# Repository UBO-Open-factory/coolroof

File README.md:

# coolroof
Développement des capteurs TOCIO pour CoolRoof

Insérer le schéma de l'architecture du projet

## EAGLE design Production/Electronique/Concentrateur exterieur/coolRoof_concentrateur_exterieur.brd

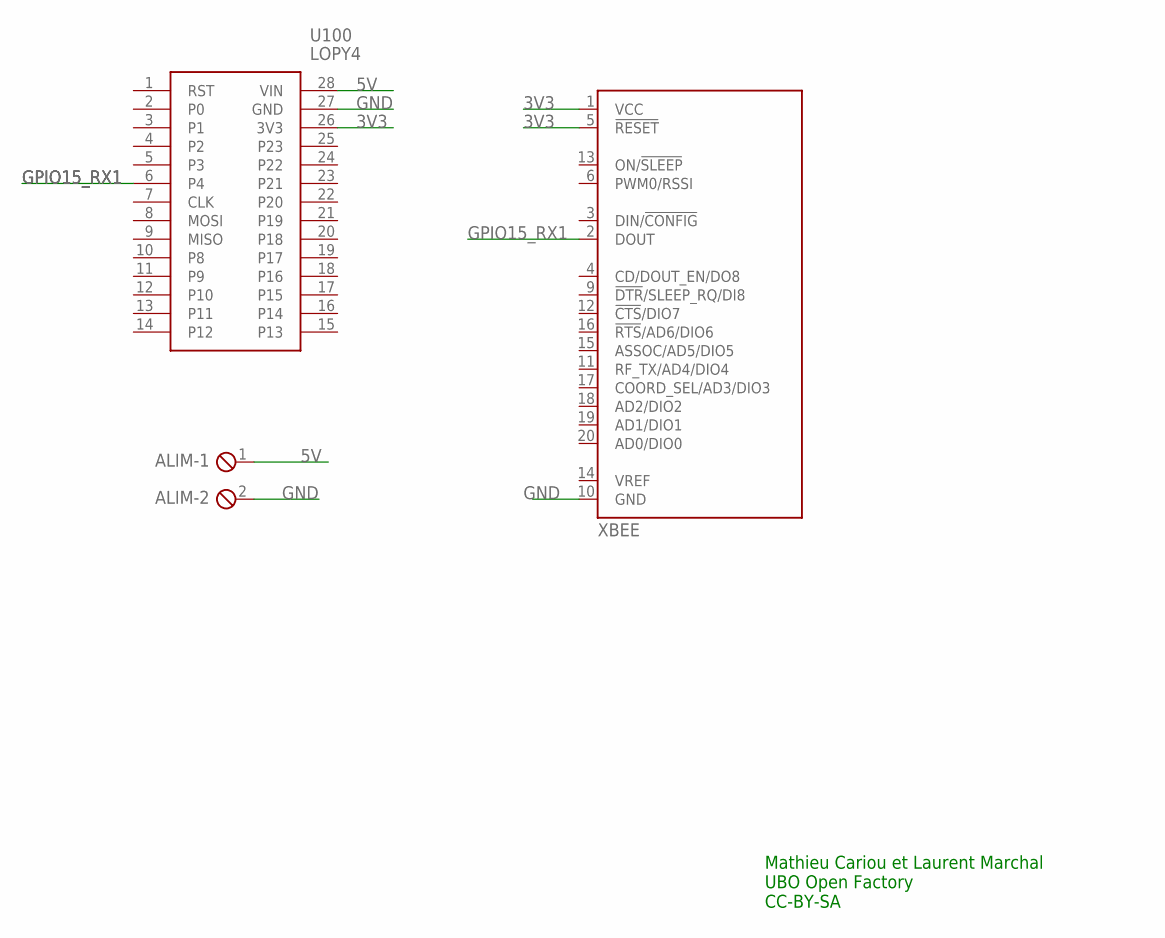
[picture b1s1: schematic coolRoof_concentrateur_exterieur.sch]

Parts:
ALIM: MPT2; 2POL254
U100: LOPY4
U101: XBEE

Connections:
3V3: U100.26 (3V3), U101.1 (VCC), U101.5 (!RESET)
5V: ALIM.1, U100.28 (VIN)
GND: ALIM.2, U100.27 (GND), U101.10 (GND)
GPIO15_RX1: U100.6 (P4), U101.2 (DOUT)

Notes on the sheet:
Mathieu Cariou et Laurent Marchal UBO Open Factory CC-BY-SA

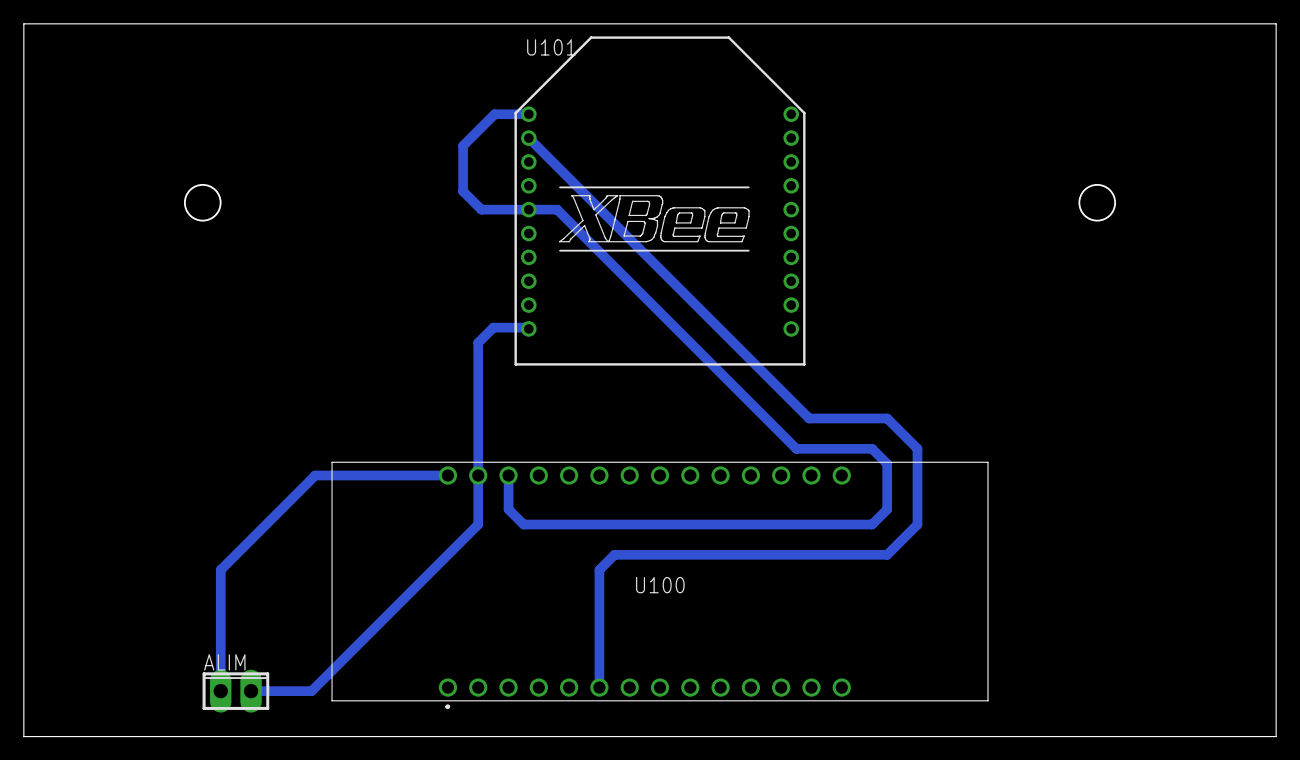
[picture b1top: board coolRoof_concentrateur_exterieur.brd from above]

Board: 2 copper layers, 105.0 x 59.8 mm, 3 parts (0 on the bottom side), 4 nets.

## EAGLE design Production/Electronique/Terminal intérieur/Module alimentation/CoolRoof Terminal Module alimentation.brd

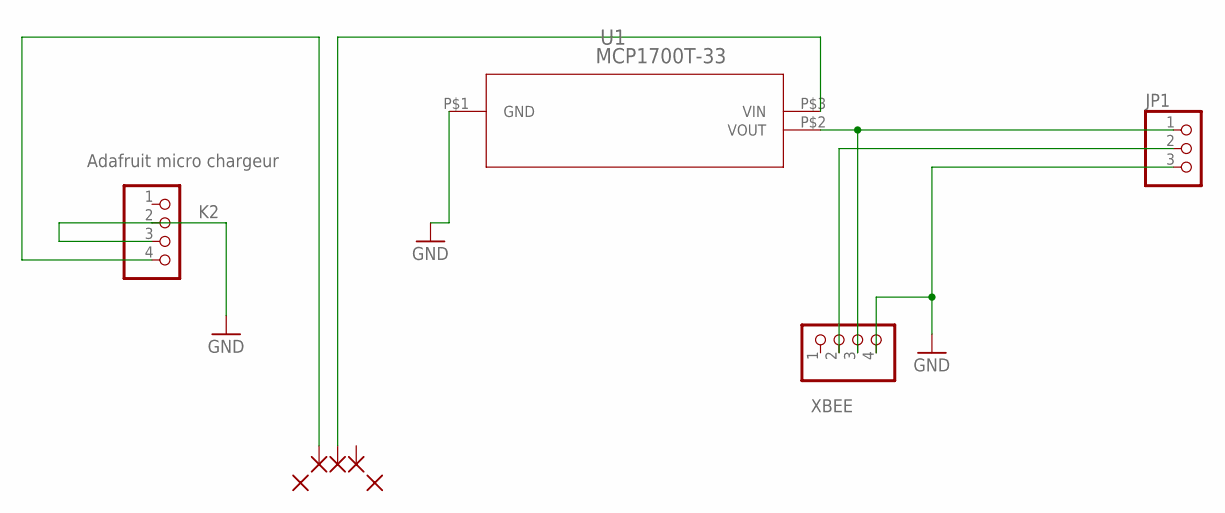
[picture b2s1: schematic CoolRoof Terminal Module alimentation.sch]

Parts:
JP1: PINHD-1X3; 1X03
K2: Adafruit micro chargeur; 1X04
PAD1, PAD2, PAD3: 1,6/0,8
PAD4, PAD5: N_2,0/1,5; 2,0/1,5
U1: MCP1700T-33; SOT-23
XBEE: PINHD-1X4; 1X04

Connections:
GND: JP1.3, K2.2, K2.3, U1.P$1 (GND), XBEE.4
unnamed: JP1.1, U1.P$2 (VOUT), XBEE.3
unnamed: JP1.2, XBEE.2
unnamed: K2.4, PAD1.1
unnamed: PAD2.1, U1.P$3 (VIN)

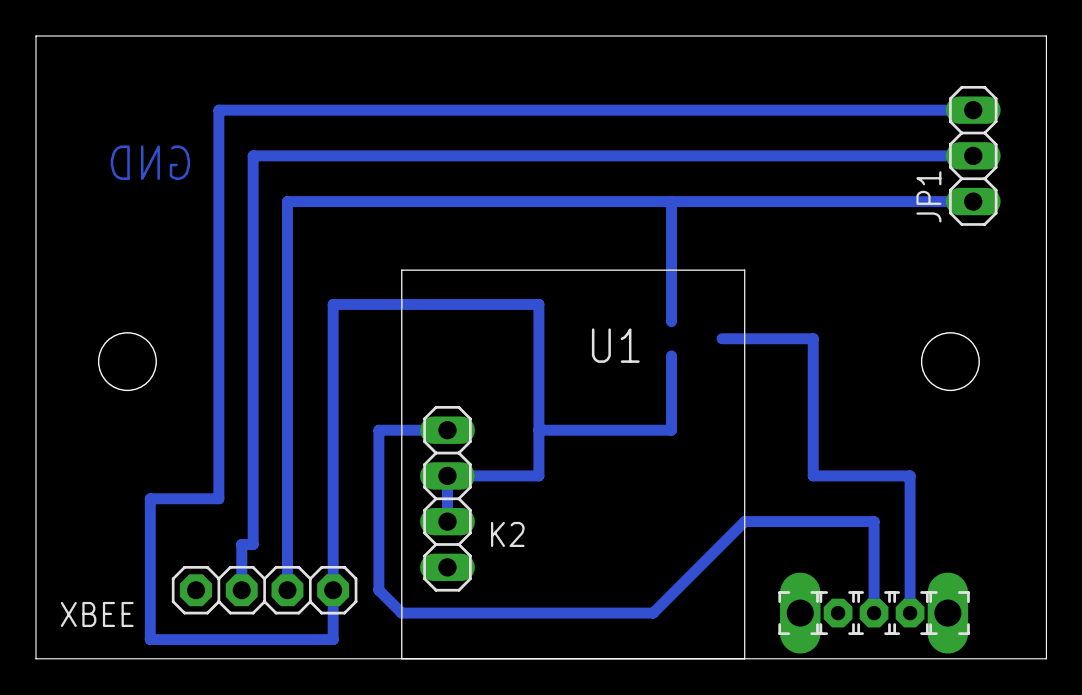
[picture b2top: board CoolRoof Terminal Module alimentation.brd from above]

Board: 2 copper layers, 56.1 x 34.6 mm, 9 parts (1 on the bottom side), 5 nets.

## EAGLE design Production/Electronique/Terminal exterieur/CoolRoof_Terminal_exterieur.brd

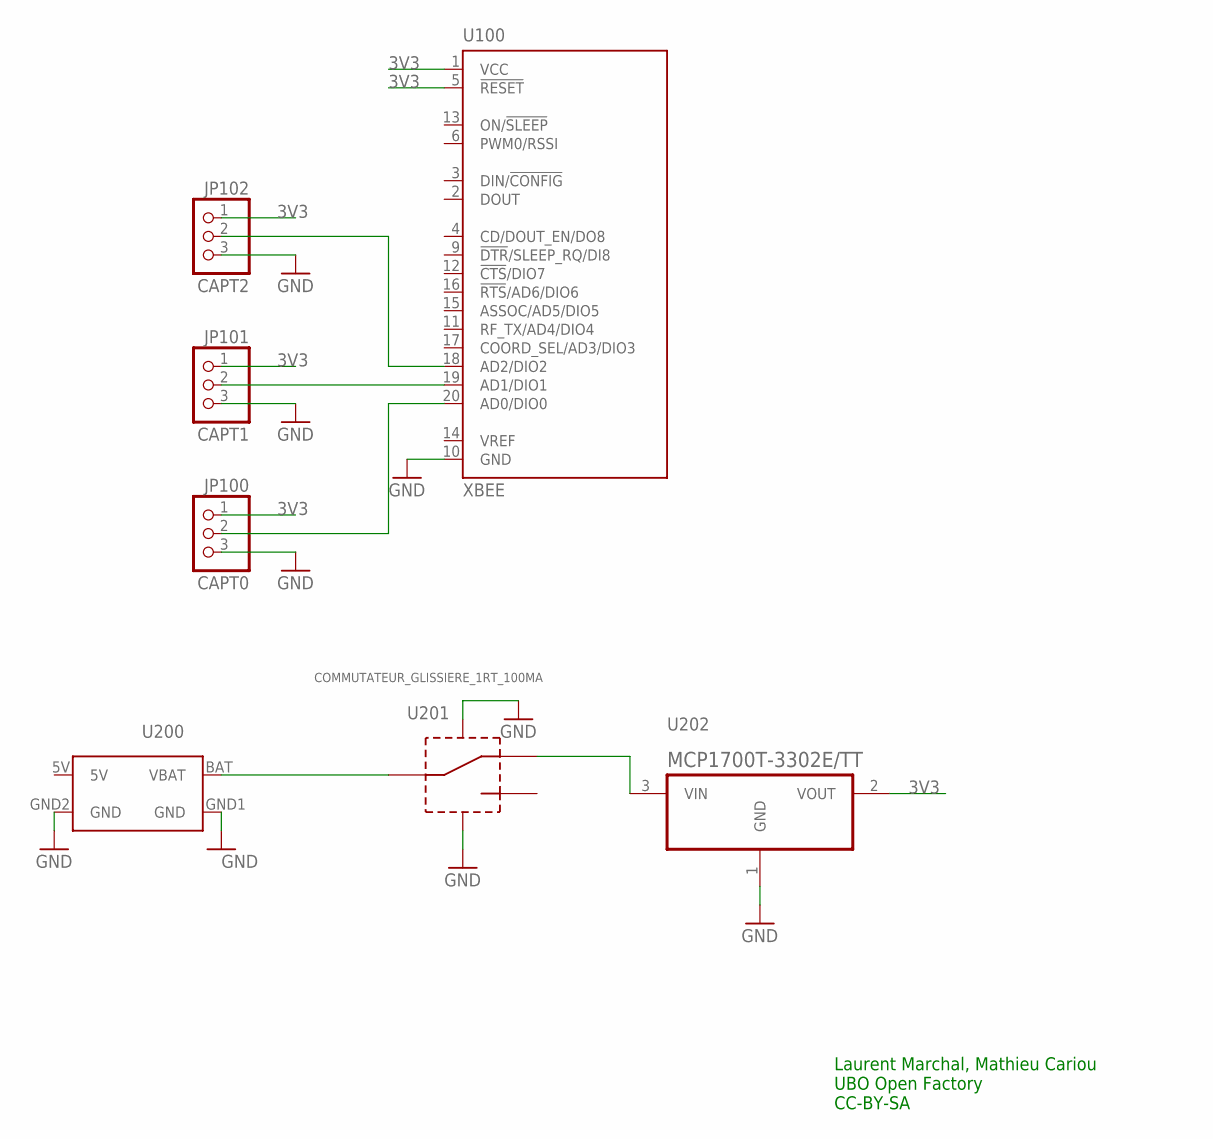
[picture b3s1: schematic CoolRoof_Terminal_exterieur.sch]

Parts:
JP100: CAPT0; 1X03
JP101: CAPT1; 1X03
JP102: CAPT2; 1X03
U100: XBEE
U200: MICROUSB-LIPO-CHARGEUR-ADAFRUITMICRO-USB-CHARGEUR; MICROUSB-LIPO-CHARGEUR-ADAFRUIT
U201: COMMUTATEUR_GLISSIERE_1RT_100MA
U202: MCP1700T-3302E/TT; SOT95P237X112-3N

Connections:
3V3: JP100.1, JP101.1, JP102.1, U100.1 (VCC), U100.5 (!RESET), U202.2 (VOUT)
GND: JP100.3, JP101.3, JP102.3, U100.10 (GND), U200.GND1 (GND), U200.GND2 (GND), U201.GNDA, U201.GNDB, U202.1 (GND)
unnamed: JP100.2, U100.20 (AD0/DIO0)
unnamed: U200.BAT (VBAT), U201.COM
unnamed: U201.OUTB (OUT2), U202.3 (VIN)
unnamed: JP101.2, U100.19 (AD1/DIO1)
unnamed: JP102.2, U100.18 (AD2/DIO2)

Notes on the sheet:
Laurent Marchal, Mathieu Cariou UBO Open Factory CC-BY-SA

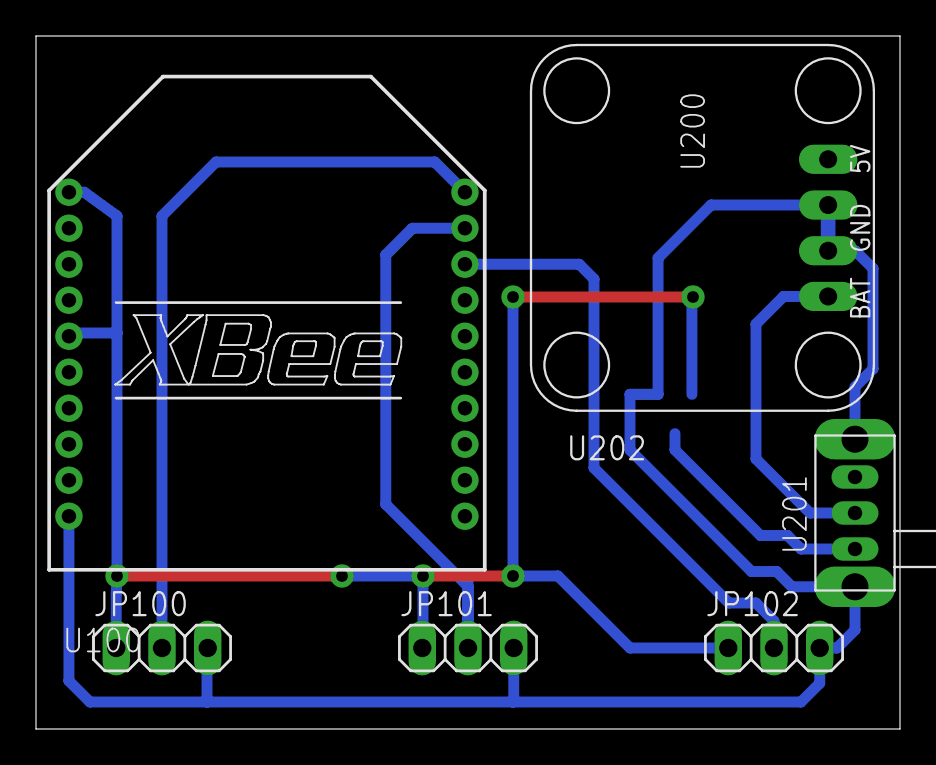
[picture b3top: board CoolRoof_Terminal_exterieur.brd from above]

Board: 2 copper layers, 48.0 x 38.5 mm, 7 parts (1 on the bottom side), 7 nets.

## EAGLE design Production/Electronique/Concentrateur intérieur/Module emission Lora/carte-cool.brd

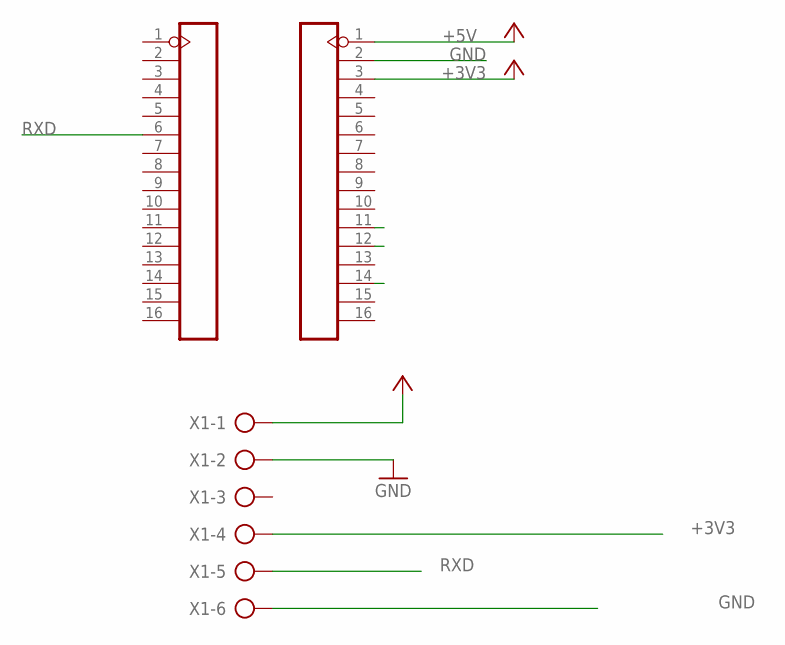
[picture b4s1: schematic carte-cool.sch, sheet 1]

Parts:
J1, J2: 16p-2.54; H16-2.54
X1: AK500/6-H

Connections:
+3V3: J2.3, X1.4
+5V: J2.1, X1.1
GND: J2.2, X1.2, X1.6
P13: J2.14
P15: J2.12
P16: J2.11
RXD: J1.6, X1.5

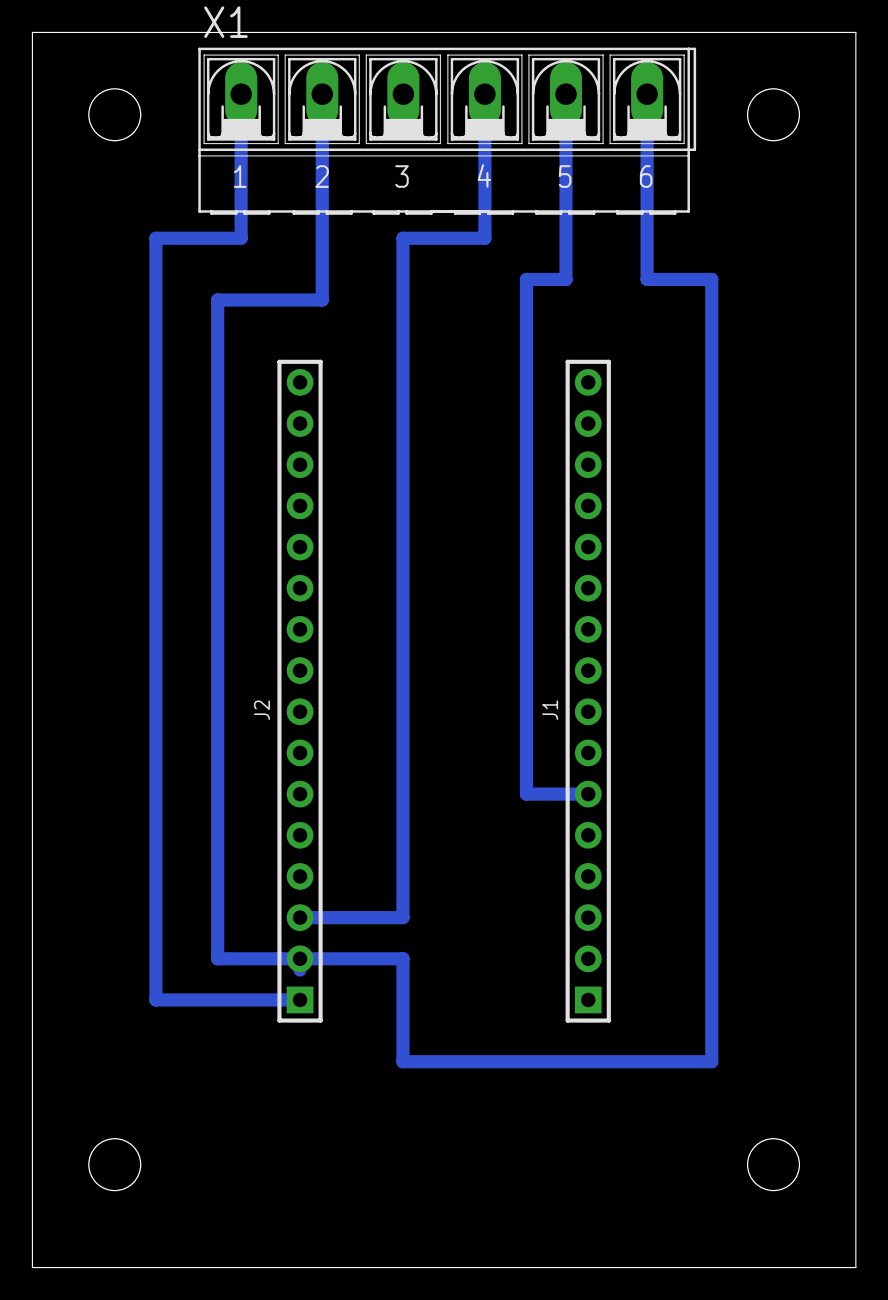
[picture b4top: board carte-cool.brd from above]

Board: 2 copper layers, 50.8 x 76.2 mm, 3 parts (0 on the bottom side), 4 nets.

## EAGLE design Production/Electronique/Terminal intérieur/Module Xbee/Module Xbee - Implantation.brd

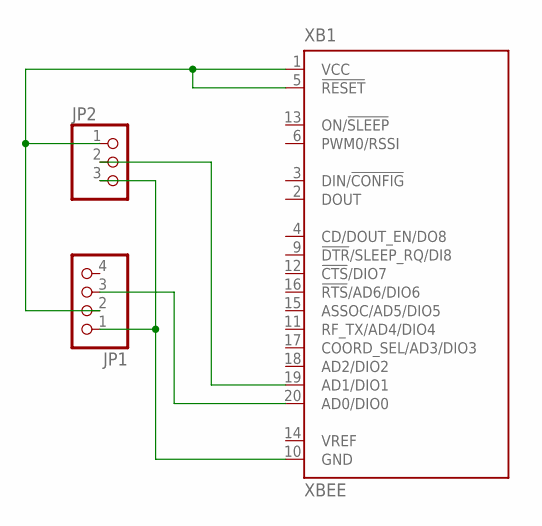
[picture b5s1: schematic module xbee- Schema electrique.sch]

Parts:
JP1: PINHD-1X4; 1X04
JP2: PINHD-1X3; 1X03
XB1: XBEE

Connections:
unnamed: JP1.2, JP2.1, XB1.1 (VCC), XB1.5 (!RESET)
unnamed: JP1.1, JP2.3, XB1.10 (GND)
unnamed: JP1.3, XB1.20 (AD0/DIO0)
unnamed: JP2.2, XB1.19 (AD1/DIO1)

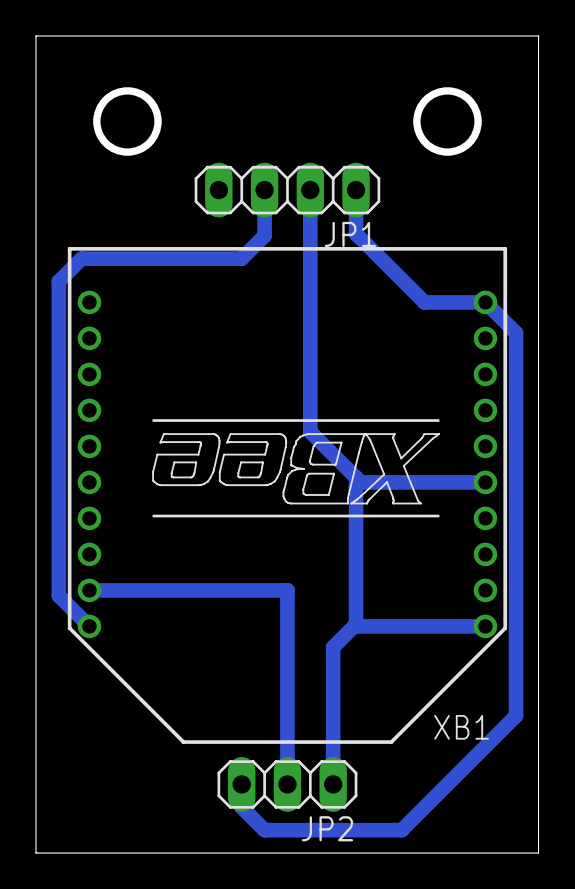
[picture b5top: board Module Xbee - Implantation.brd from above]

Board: 2 copper layers, 27.9 x 45.4 mm, 3 parts (0 on the bottom side), 4 nets.

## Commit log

2021-05-04 ajout trace de debug et modification
    modification
    - ajout variable norme_hf (définition des norme de fréquence pour le lorawan)
    -retrait fonction wakup sur pin P3 (le lopy ne se met pas en veille donc pas besoin de le réveiller)
    - supression de "i=i+1" dans la boucle: for i in range(0,longueur)
    -ajout led blanc faible luminosité l'or de l'attente de donnée
    - ajout led orange pour indicateur visuel de réception de data
2021-06-16 ajout PCB EAGLE reseau ext
    - Concentrateur
    - terminal
2021-06-16 ajout README PCB
2021-06-16 ignorer les .lck
2021-06-16 ajout contraintes mécanique PCB terminaux extérieur
2021-06-16 ajout contrainte mécanique concentrateur extérieur
2021-06-17 modif routage carte terminaux extérieur
2021-06-18 Modif légère du PCB terminal exterieur CoolRoof
2021-06-18 Deplacement du Label U200
2021-06-18 modif légere PCB terminaux extérieur
    - modif enplacement label U202
2021-06-18 Commit mais je ne sais pas pourquoi...
2021-06-18 Remplacement du microchargeur par version aux pastilles plus larges
2021-07-06 ajout programme LoPy_EXT
    ajout des fichier
    -boot.py
    -main.py
    du programme
    +
    ajout Readme.md
2021-11-03 Premiere reorganisation
2021-11-03 Déplacement programme Lopy
2021-12-13 Mise à jour du repository
    Adjonction des procédures de programmation TOCIO, Back office Orange et configuration des Xbee
